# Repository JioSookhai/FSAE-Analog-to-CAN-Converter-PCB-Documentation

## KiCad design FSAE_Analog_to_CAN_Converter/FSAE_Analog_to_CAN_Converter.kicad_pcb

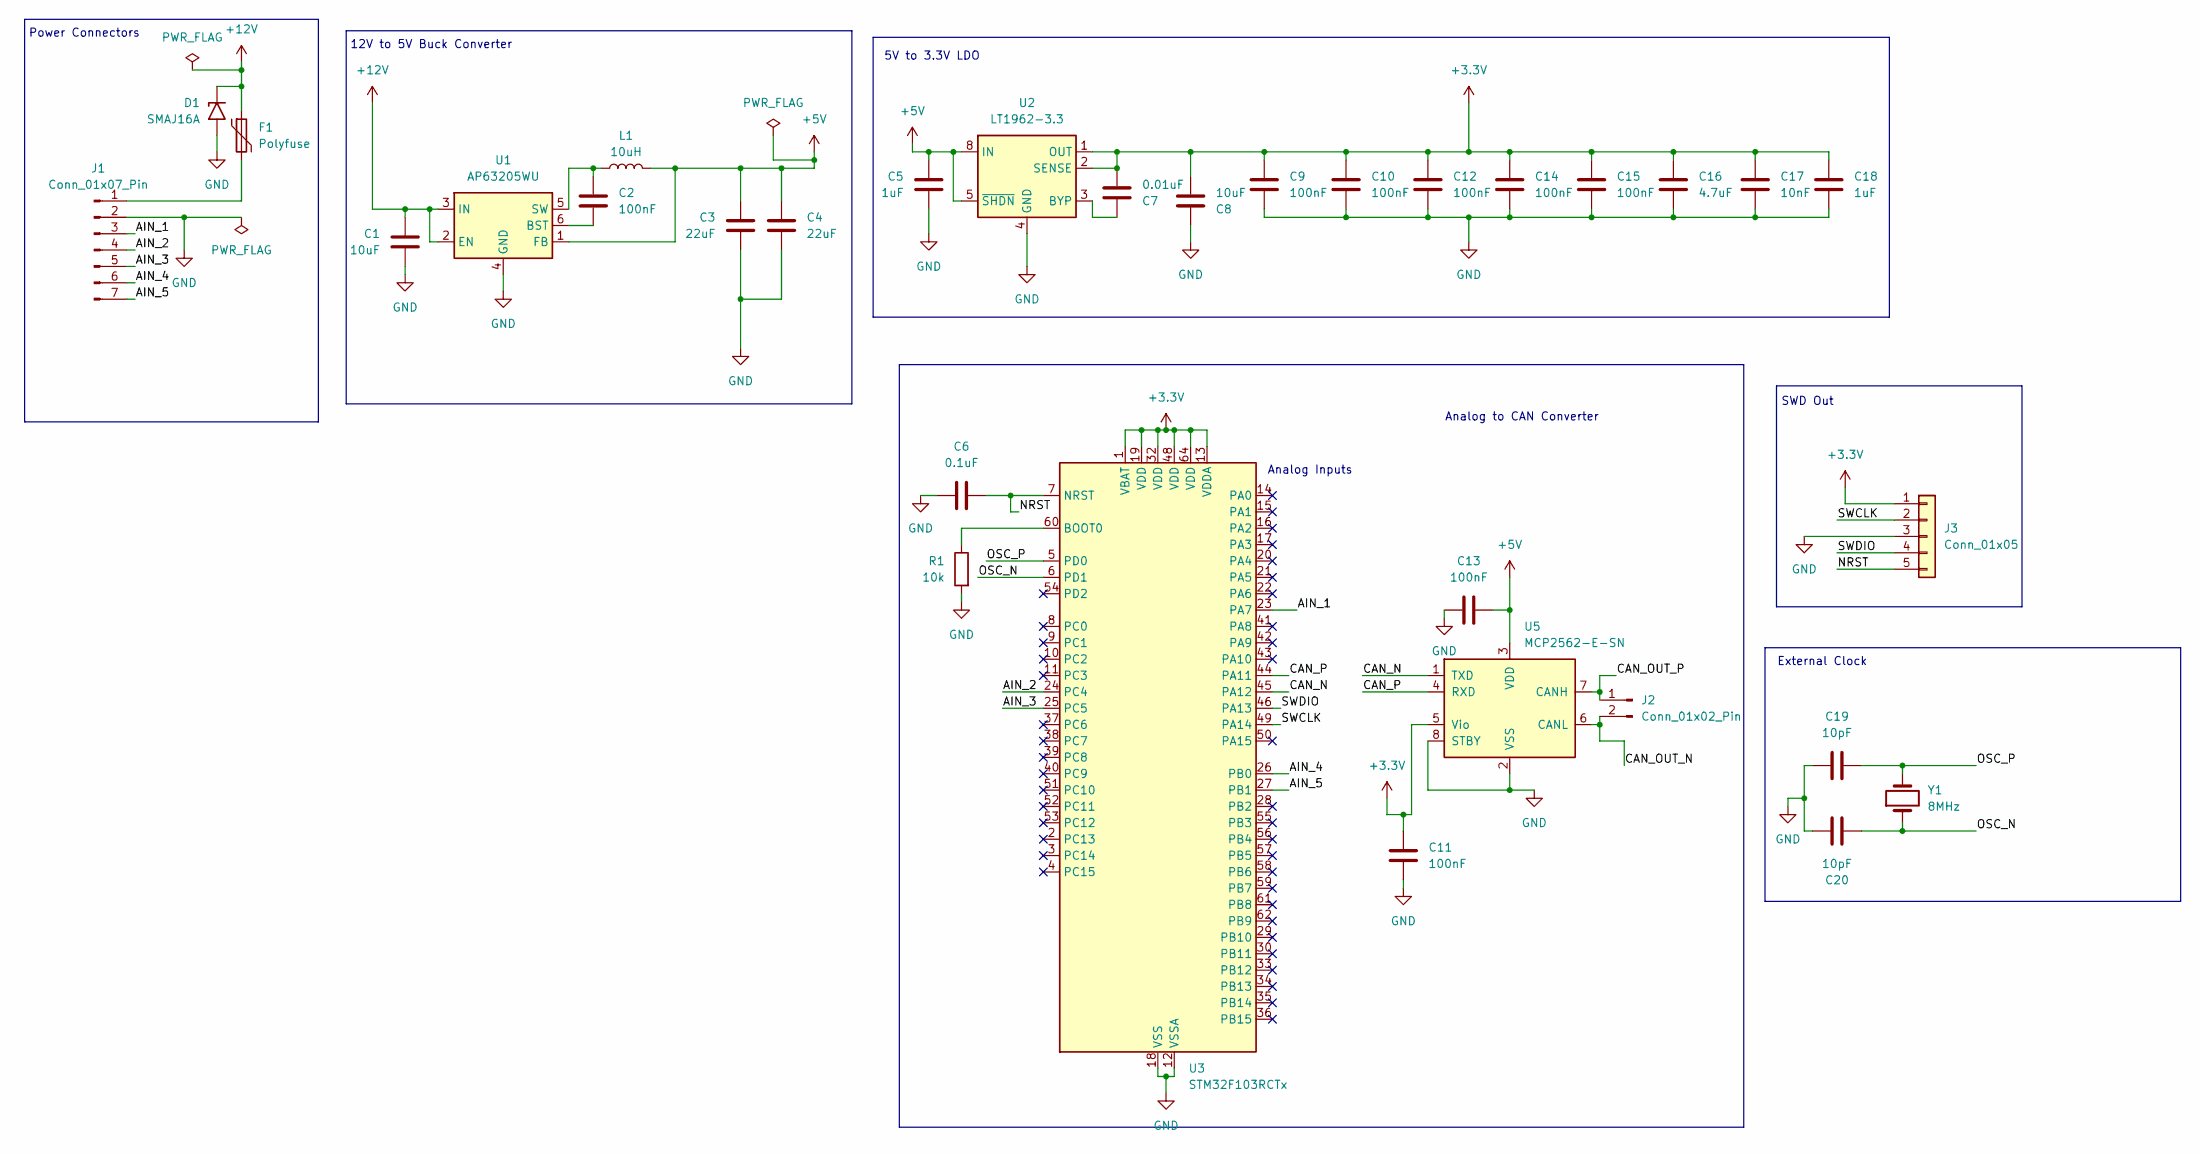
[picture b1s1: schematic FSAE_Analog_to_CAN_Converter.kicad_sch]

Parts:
C1, C8: 10uF; C_0603_1608Metric_Pad1.08x0.95mm_HandSolder
C2, C9, C10, C11, C12, C13, C14, C15: 100nF; C_0603_1608Metric_Pad1.08x0.95mm_HandSolder
C3, C4: 22uF; C_0603_1608Metric_Pad1.08x0.95mm_HandSolder
C5, C18: 1uF; C_0603_1608Metric_Pad1.08x0.95mm_HandSolder
C6: 0.1uF; C_0603_1608Metric_Pad1.08x0.95mm_HandSolder
C7: 0.01uF; C_0603_1608Metric_Pad1.08x0.95mm_HandSolder
C16: 4.7uF; C_0603_1608Metric_Pad1.08x0.95mm_HandSolder
C17: 10nF; C_0603_1608Metric_Pad1.08x0.95mm_HandSolder
C19, C20: 10pF; C_0603_1608Metric_Pad1.08x0.95mm_HandSolder
D1: SMAJ16A; D_SMA
F1: Polyfuse; Fuse_1812_4532Metric_Pad1.30x3.40mm_HandSolder
J1: Conn_01x07_Pin; Molex_Micro-Fit_3.0_43650-0700_1x07_P3.00mm_Horizontal
J2: Conn_01x02_Pin; Molex_Micro-Fit_3.0_43045-0212_2x01_P3.00mm_Vertical
J3: Conn_01x05; PinHeader_1x05_P2.54mm_Vertical
L1: 10uH; L_1210_3225Metric_Pad1.42x2.65mm_HandSolder
R1: 10k; R_0805_2012Metric_Pad1.20x1.40mm_HandSolder
U1: AP63205WU; TSOT-23-6
U2: LT1962-3.3; MSOP-8_3x3mm_P0.65mm
U3: STM32F103RCTx; LQFP-64_10x10mm_P0.5mm
U5: MCP2562-E-SN; SOIC-8_3.9x4.9mm_P1.27mm
Y1: 8MHz; Crystal_SMD_2012-2Pin_2.0x1.2mm_HandSoldering

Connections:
+3.3V: C7.2, C8.2, C9.1, C10.1, C11.2, C12.1, C14.1, C15.1, C16.1, C17.1, C18.1, J3.1, U2.1 (OUT), U2.2 (SENSE), U3.1 (VBAT), U3.13 (VDDA), U3.19 (VDD), U3.32 (VDD), U3.48 (VDD), U3.64 (VDD), U5.5 (Vio)
+5V: C3.1, C4.1, C5.1, C13.2, L1.2, U1.1 (FB), U2.5 (~SHDN), U2.8 (IN), U5.3 (VDD)
+12V: C1.1, D1.1 (A1), F1.1, U1.2 (EN), U1.3 (IN)
/AIN_1: J1.3, U3.23 (PA7)
/AIN_2: J1.4, U3.24 (PC4)
/AIN_3: J1.5, U3.25 (PC5)
/AIN_4: J1.6, U3.26 (PB0)
/AIN_5: J1.7, U3.27 (PB1)
/CAN_N: U3.45 (PA12), U5.1 (TXD)
/CAN_OUT_N: J2.2, U5.6 (CANL)
/CAN_OUT_P: J2.1, U5.7 (CANH)
/CAN_P: U3.44 (PA11), U5.4 (RXD)
/NRST: C6.2, J3.5, U3.7 (NRST)
/OSC_N: C20.2, U3.6 (PD1), Y1.1
/OSC_P: C19.2, U3.5 (PD0), Y1.2
/SWCLK: J3.2, U3.49 (PA14)
/SWDIO: J3.4, U3.46 (PA13)
GND: C1.2, C3.2, C4.2, C5.2, C6.1, C8.1, C9.2, C10.2, C11.1, C12.2, C13.1, C14.2, C15.2, C16.2, C17.2, C18.2, C19.1, C20.1, D1.2 (A2), J1.2, J3.3, R1.2, U1.4 (GND), U2.4 (GND), U3.12 (VSSA), U3.18 (VSS), U3.31 (VSS), U3.47 (VSS), U3.63 (VSS), U5.2 (VSS), U5.8 (STBY)
unnamed: F1.2, J1.1
unnamed: C2.2, U1.6 (BST)
unnamed: C2.1, L1.1, U1.5 (SW)
unnamed: C7.1, U2.3 (BYP)
unnamed: R1.1, U3.60 (BOOT0)

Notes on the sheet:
Power Connectors
5V to 3.3V LDO
Analog Inputs
External Clock
Analog to CAN Converter
SWD Out
12V to 5V Buck Converter

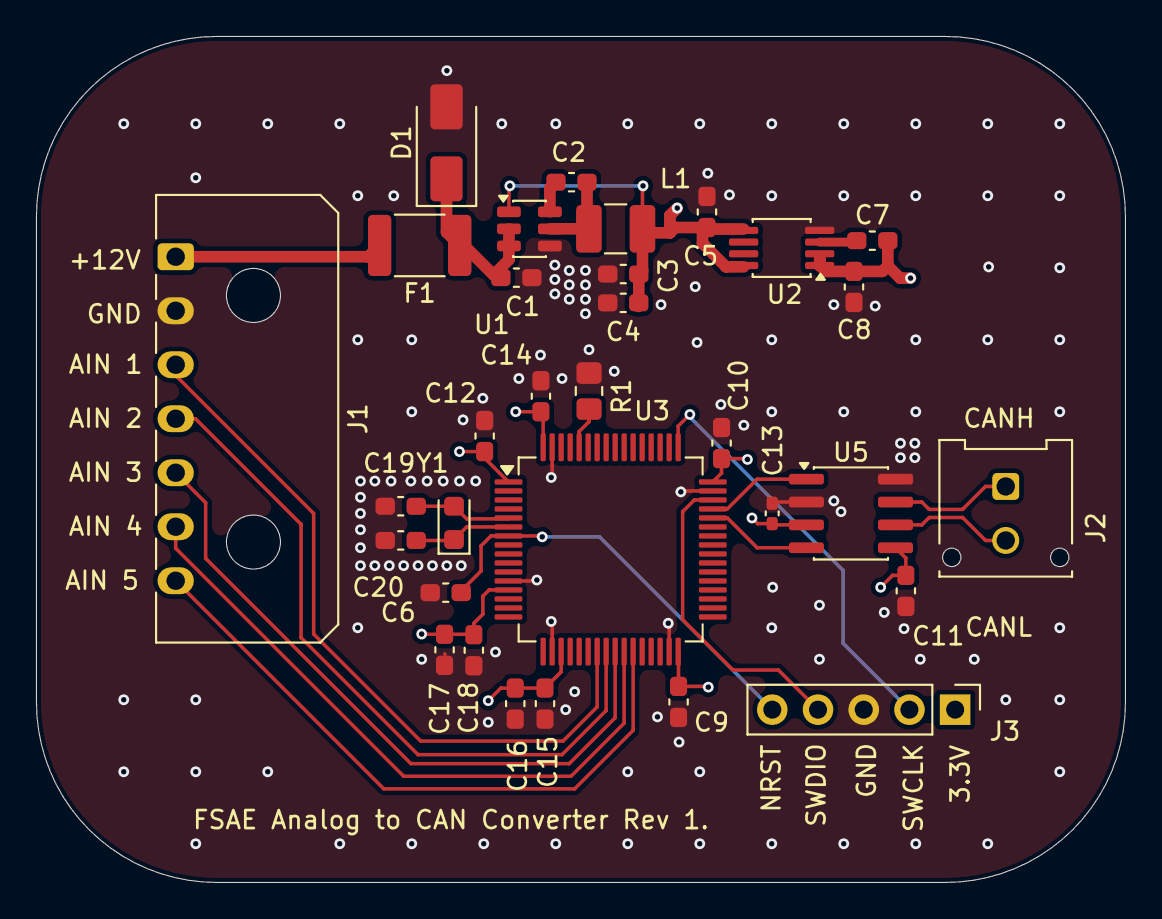
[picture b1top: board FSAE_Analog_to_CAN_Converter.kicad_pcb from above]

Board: 4 copper layers, 60.5 x 47.0 mm, 32 parts (0 on the bottom side), 23 nets.
